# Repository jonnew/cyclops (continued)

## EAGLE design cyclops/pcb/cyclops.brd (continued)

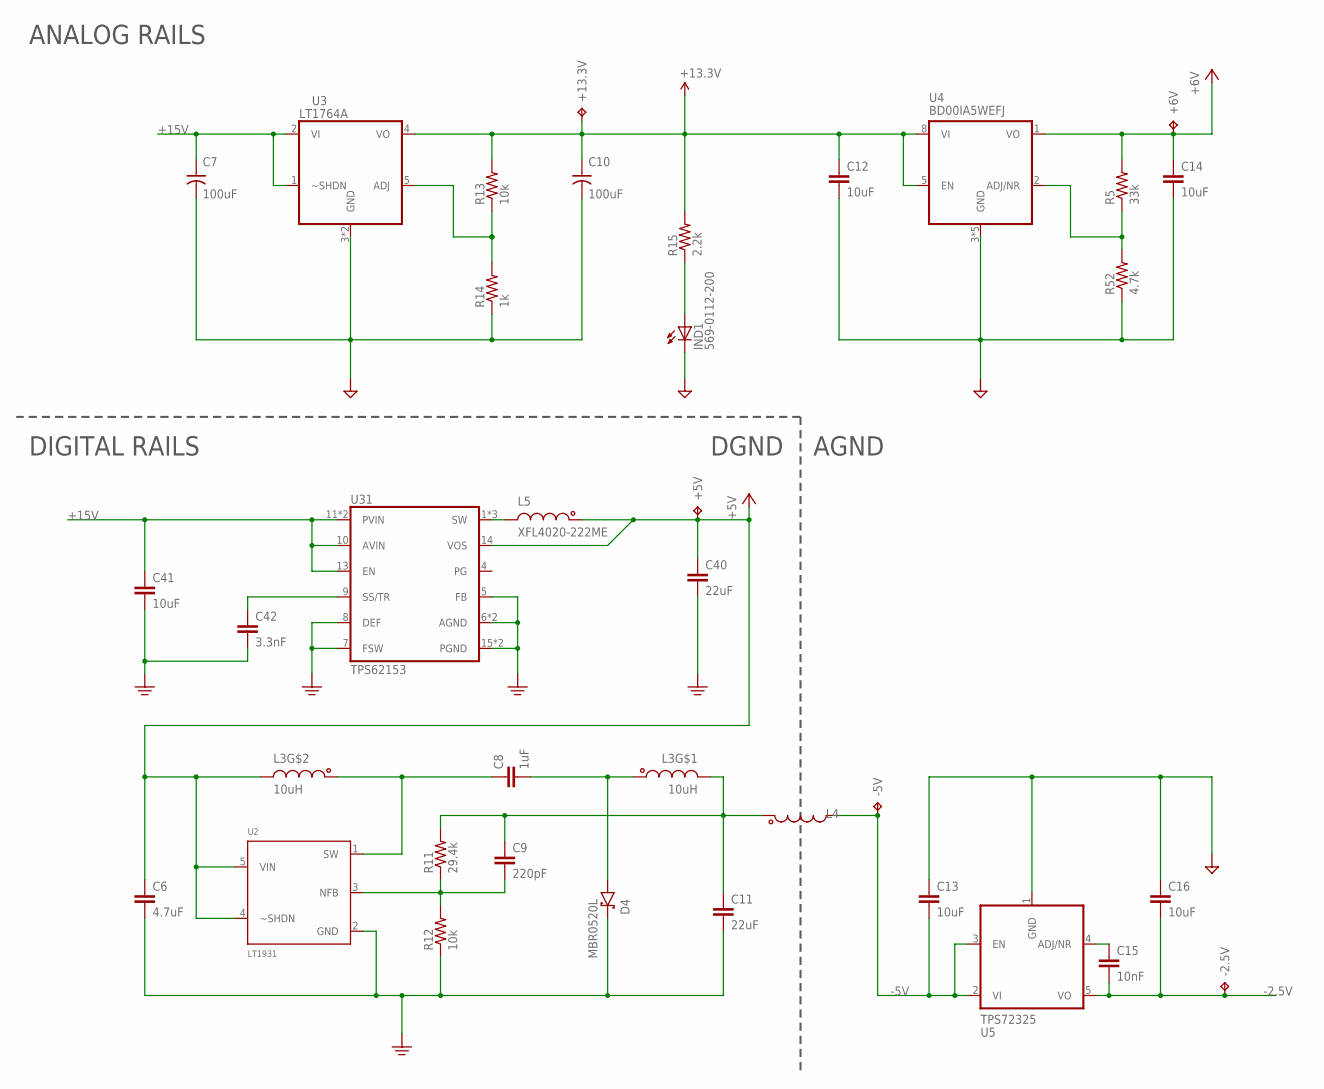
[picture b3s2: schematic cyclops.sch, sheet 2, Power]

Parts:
+5V, +6V, +13.3V: RCU-0C; RC0603
-2.5V, -5V: RCU-0C; RC0603
C6: 4.7uF; 1206
C7, C10: 100uF; 153CLV-0807
C8: 1uF; 1206
C9: 220pF; 0603
C11, C40: 22uF; 1210
C12, C13, C14, C16, C41: 10uF; 1206
C15: 10nF; 0603
C42: 3.3nF; 0603
D4: MBR0520L; SOD123
IND: 569-0112-200; 569-011X-X00_LED_ARRAY
L3: 10uH; CLS62
L4: MPZ1608; 0603
L5: XFL4020-222ME; 4020
R5: 33k; 0603
R11: 29.4k; 0603
R12, R13: 10k; 0603
R14: 1k; 0603
R15: 2.2k; 0603
R52: 4.7k; 0603
U2: LT1931; SOT95P310X175-5N
U3: LT1764A; 5-DDPAK
U4: BD00IA5WEFJ; SOIC127P600X175-9N
U5: TPS72325; SOT-23-5
U31: TPS62153; VQFN16

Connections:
+5V: +5V.1, C6.1, C40.1, L3.3 (2), L5.1, U2.4 (~SHDN), U2.5 (VIN), U31.14 (VOS); also elsewhere on the board
+6V: +6V.1, C14.1, R5.2, U4.1 (VO); also elsewhere on the board
+13.3V: +13.3V.1, C10.+, C12.1, R13.2, R15.2, U3.4 (VO), U4.5 (EN), U4.8 (VI); also elsewhere on the board
+15V: C7.+, C41.1, U3.1 (~SHDN), U3.2 (VI), U31.10 (AVIN), U31.11 (PVIN), U31.12 (PVIN), U31.13 (EN); also elsewhere on the board
-2.5V: -2.5V.1, C15.2, C16.2, U5.5 (VO); also elsewhere on the board
-5V: -5V.1, C13.2, L4.2, U5.2 (VI), U5.3 (EN); also elsewhere on the board
GND: C6.2, C7.-, C10.-, C11.2, C12.2, C13.1, C14.2, C16.1, C40.2, C41.2, C42.2, D4.C, IND.C1 (C), R12.1, R14.1, R52.1, U2.2 (GND), U3.3 (GND), U3.TAB (GND), U4.3 (GND), U4.4 (GND), U4.6 (GND), U4.7 (GND), U4.9 (GND), U5.1 (GND), U31.5 (FB), U31.6 (AGND), U31.7 (FSW), U31.8 (DEF), U31.15 (PGND), U31.16 (PGND), U31.PAD (AGND); also elsewhere on the board
unnamed: IND.A1 (A), R15.1
unnamed: R13.1, R14.2, U3.5 (ADJ)
unnamed: C8.1, L3.2 (1), U2.1 (SW)
unnamed: C8.2, D4.A, L3.1
unnamed: C9.1, C11.1, L3.4 (2), L4.1, R11.2
unnamed: C9.2, R11.1, R12.2, U2.3 (NFB)
unnamed: R5.1, R52.2, U4.2 (ADJ/NR)
unnamed: C15.1, U5.4 (ADJ/NR)
unnamed: C42.1, U31.9 (SS/TR)
SW: L5.2, U31.1 (SW), U31.2 (SW), U31.3 (SW)

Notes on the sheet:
ANALOG RAILS
DIGITAL RAILS
AGND
DGND

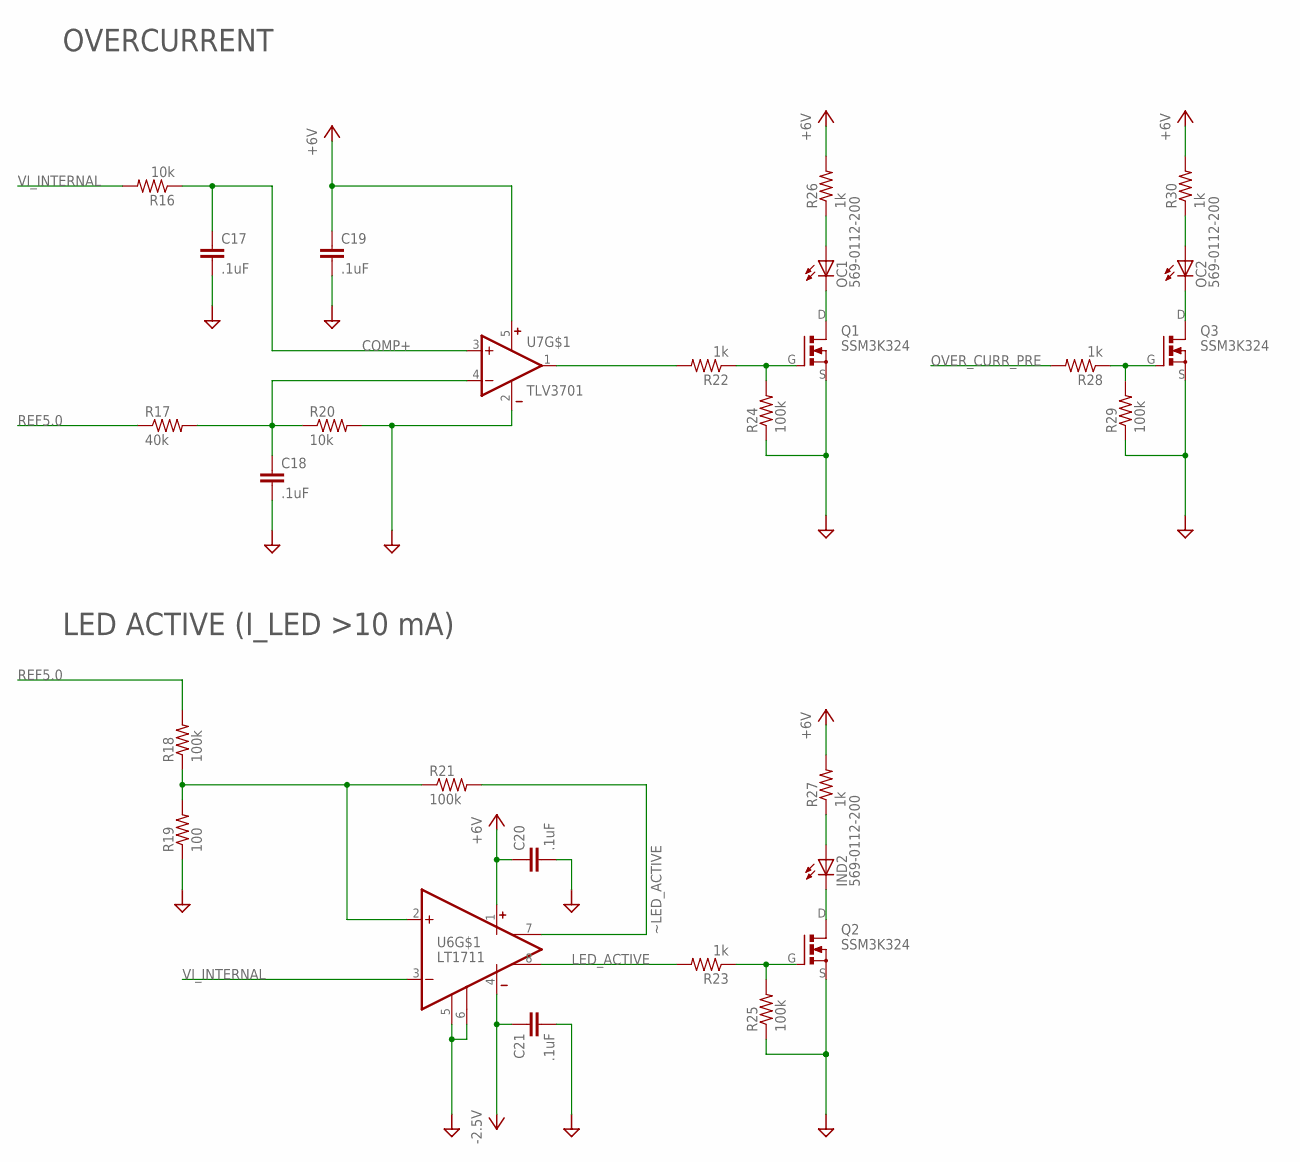
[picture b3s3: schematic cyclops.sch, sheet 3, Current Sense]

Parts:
C17, C18, C19, C20, C21: .1uF; 0603
IND: 569-0112-200; 569-011X-X00_LED_ARRAY
OC: 569-0112-200; 569-011X-X00_LED_ARRAY
Q1, Q2, Q3: SSM3K324; SOT23-GSD
R16, R20: 10k; 0603
R17: 40k; 0603
R18, R21, R24, R25, R29: 100k; 0603
R19: 100; 0603
R22, R23, R26, R27, R28, R30: 1k; 0603
U6: LT1711; SOP65P490X110-8N
U7: TLV3701; SOT-23-5

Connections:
+6V: C19.1, C20.1, R26.2, R27.2, R30.2, U6.1 (V+), U7.5 (V+); also elsewhere on the board
-2.5V: C21.1, U6.4 (V-); also elsewhere on the board
COMP+: C17.1, R16.1, U7.3 (+IN)
GND: C17.2, C18.2, C19.2, C20.2, C21.2, Q1.S, Q2.S, Q3.S, R19.1, R20.2, R24.1, R25.1, R29.1, U6.5 (LATCH), U6.6 (GND), U7.2 (V-); also elsewhere on the board
LED_ACTIVE: R23.2, U6.8 (~Q); also elsewhere on the board
unnamed: OC.A1 (A), R26.1
unnamed: C18.1, R17.2, R20.1, U7.4 (-IN)
unnamed: OC.C1 (C), Q1.D
unnamed: OC.A2 (A), R30.1
unnamed: R22.2, U7.1 (OUT)
unnamed: Q1.G, R22.1, R24.2
unnamed: Q3.G, R28.1, R29.2
unnamed: R18.1, R19.2, R21.1, U6.2 (+IN)
unnamed: IND.A2 (A), R27.1
unnamed: IND.C2 (C), Q2.D
unnamed: Q2.G, R23.1, R25.2
OC: OC.C2 (C), Q3.D
OVER_CURR_PRE: R28.2; also elsewhere on the board
REF5.0: R17.1, R18.2; also elsewhere on the board
VI_INTERNAL: R16.2, U6.3 (-IN); also elsewhere on the board
~LED_ACTIVE: R21.2, U6.7 (Q)

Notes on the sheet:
LED ACTIVE (I_LED >10 mA)
OVERCURRENT

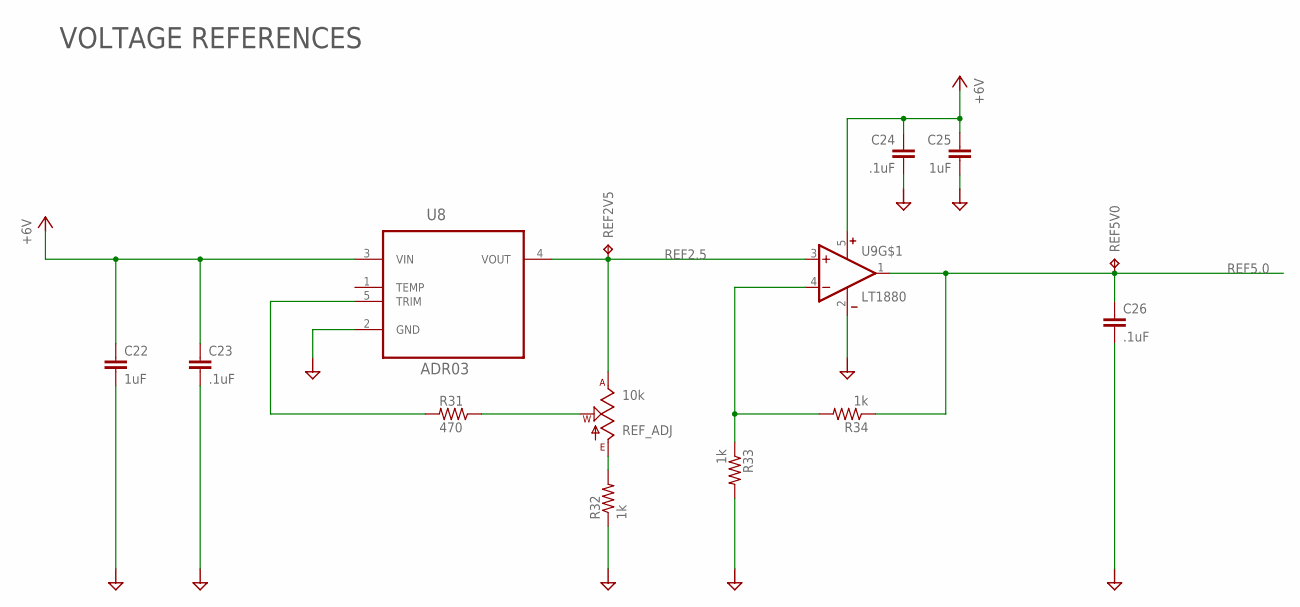
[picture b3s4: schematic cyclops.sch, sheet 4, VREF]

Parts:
C22, C25: 1uF; 0805
C23, C24, C26: .1uF; 0603
R31: 470; 0603
R32, R33, R34: 1k; 0603
REF2V5, REF5V0: RCU-0C; RC0603
REF_ADJ: 10k; SM-42/43W
U8: ADR03; SOT65P210X110-5N
U9: LT1880; SOT95P310X175-5N

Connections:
+6V: C22.1, C23.1, C24.1, C25.1, U8.3 (VIN), U9.5 (V+); also elsewhere on the board
GND: C22.2, C23.2, C24.2, C25.2, C26.2, R32.1, R33.2, U8.2 (GND), U9.2 (V-); also elsewhere on the board
unnamed: R32.2, REF_ADJ.3 (E)
unnamed: R33.1, R34.2, U9.4 (-IN)
unnamed: R31.2, U8.5 (TRIM)
unnamed: R31.1, REF_ADJ.2 (W)
REF2.5: REF2V5.1, REF_ADJ.1 (A), U8.4 (VOUT), U9.3 (+IN); also elsewhere on the board
REF5.0: C26.1, R34.1, REF5V0.1, U9.1 (OUT); also elsewhere on the board

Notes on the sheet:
VOLTAGE REFERENCES

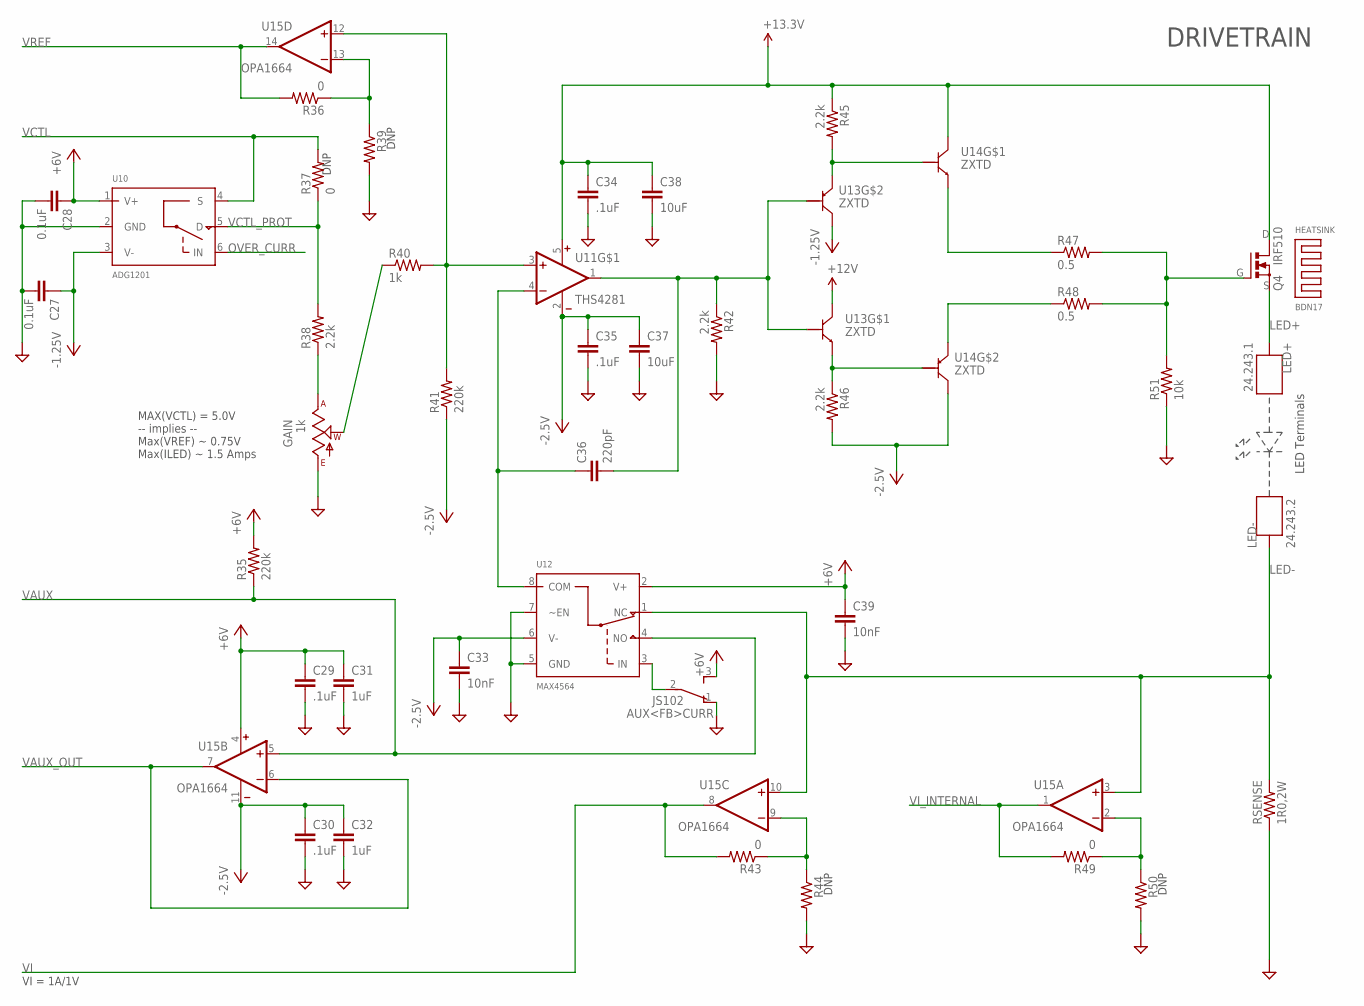
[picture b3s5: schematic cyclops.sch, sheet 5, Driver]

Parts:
AUX<FB>CURR: JS102; JS102011SAQN
C27, C28: 0.1uF; 0603
C29, C30, C34, C35: .1uF; 0603
C31, C32: 1uF; 0805
C33, C39: 10nF; 0603
C36: 220pF; 0603
C37, C38: 10uF; 1206
GAIN: 1k; 3310C-001
HEATSINK: BDN17
LED+: 24.243.1; A-2107
LED-: 24.243.2; A-2107
Q4: IRF510; TO-262_01
R35, R41: 220k; 0603
R36, R37, R43, R49: 0; 0603
R38, R42, R45, R46: 2.2k; 0603
R39, R44, R50: R_0603; 0603
R40: 1k; 0603
R47, R48: 0.5; 0603
R51: 10k; 0603
RSENSE: 1R0,2W; 2512
U10: ADG1201; SOT23-6
U11: THS4281; SOT95P310X175-5N
U12: MAX4564; SOT65P300X175-N
U13, U14: ZXTD; SOT23-6
U15: OPA1664; SO14

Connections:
+6V: AUX<FB>CURR.3, C28.1, C29.1, C31.1, C39.1, R35.2, U10.1 (V+), U12.2 (V+), U15.4 (V+); also elsewhere on the board
+13.3V: C34.1, C38.1, Q4.D, R45.1, U11.5 (V+), U13.1 (C), U14.1 (C); also elsewhere on the board
-2.5V: C27.1, C30.1, C32.1, C33.1, C35.1, C37.1, R41.1, R46.2, U10.3 (V-), U11.2 (V-), U12.6 (V-), U13.3 (C), U14.3 (C), U15.11 (V-); also elsewhere on the board
COM: C36.1, U11.4 (-IN), U12.8 (COM)
GND: AUX<FB>CURR.1, C27.2, C28.2, C29.2, C30.2, C31.2, C32.2, C33.2, C34.2, C35.2, C37.2, C38.2, C39.2, GAIN.1 (E), R39.2, R42.2, R44.2, R50.2, R51.1, RSENSE.1, U10.2 (GND), U12.5 (GND), U12.7 (~EN); also elsewhere on the board
IN: AUX<FB>CURR.2, U12.3 (IN)
LED+: LED+.1, LED+.2, Q4.S; also elsewhere on the board
LED-: LED-.1, LED-.2, RSENSE.2, U12.1 (NC), U15.3 (+IN), U15.10 (+IN); also elsewhere on the board
unnamed: R45.2, U13.4 (E), U14.2 (B)
unnamed: R36.1, R39.1, U15.13 (-IN)
unnamed: R46.1, U13.6 (E), U14.5 (B)
unnamed: R49.1, R50.1, U15.2 (-IN)
unnamed: C36.2, R42.1, U11.1 (OUT), U13.2 (B), U13.5 (B)
unnamed: R43.1, R44.1, U15.9 (-IN)
unnamed: R48.1, U14.4 (E)
unnamed: R47.1, U14.6 (E)
unnamed: Q4.G, R47.2, R48.2, R51.2
unnamed: GAIN.2 (W), R40.1
OVER_CURR: U10.6 (IN); also elsewhere on the board
VAUX: R35.1, U12.4 (NO), U15.5 (+IN); also elsewhere on the board
VAUX_OUT: U15.6 (-IN), U15.7 (OUT); also elsewhere on the board
VCTL: R37.2, U10.4 (S); also elsewhere on the board
VCTL_PROT: R37.1, R38.2, U10.5 (D)
VCTL_PROTECT: GAIN.3 (A), R38.1
VI: R43.2, U15.8 (OUT); also elsewhere on the board
VI_INTERNAL: R49.2, U15.1 (OUT); also elsewhere on the board
VREF: R36.2, U15.14 (OUT); also elsewhere on the board
_VREF: R40.2, R41.2, U11.3 (+IN), U15.12 (+IN)

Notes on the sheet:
LED Terminals
MAX(VCTL) = 5.0V -- implies -- Max(VREF) ~ 0.75V Max(ILED) ~ 1.5 Amps
VI = 1A/1V
DRIVETRAIN
DNP

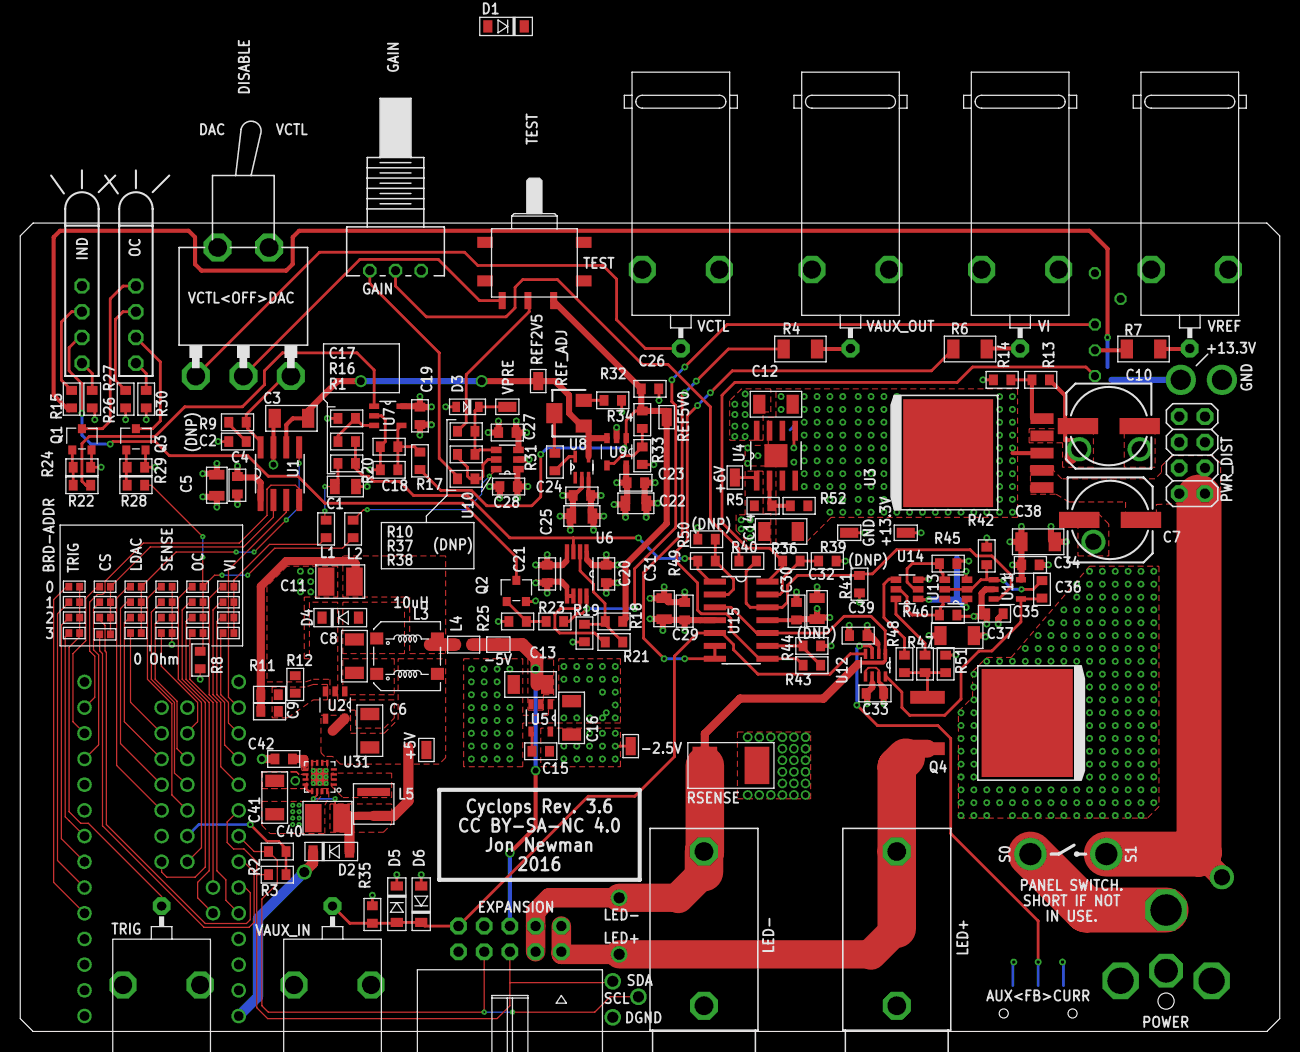
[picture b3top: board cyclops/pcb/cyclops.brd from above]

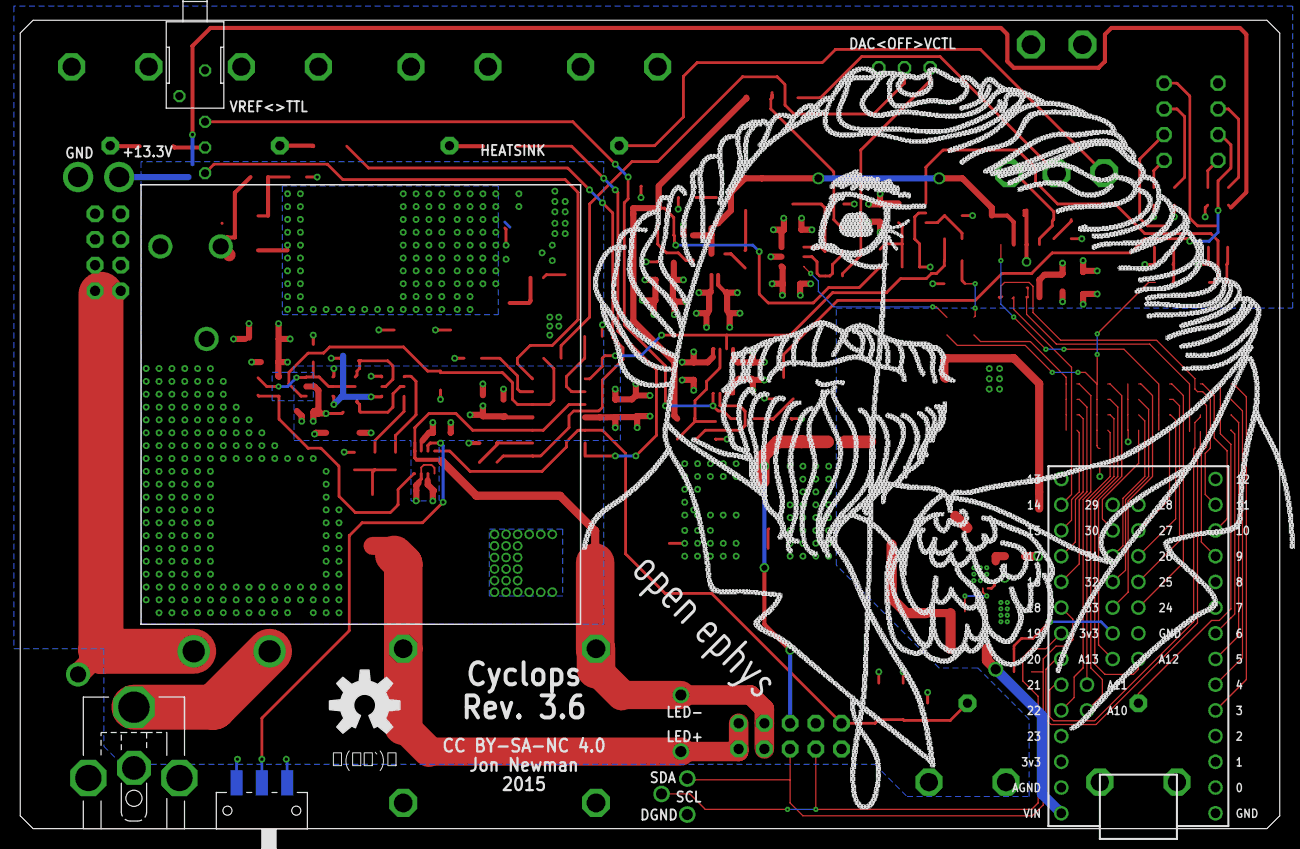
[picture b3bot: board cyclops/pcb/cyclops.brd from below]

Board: 4 copper layers, 124.5 x 79.9 mm, 183 parts (8 on the bottom side), 107 nets.

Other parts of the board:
U$30: OPEN_EPHYS_LOGO
U$56: CYCLOPS_LOGO
U$60: OSHW-LOGO-L

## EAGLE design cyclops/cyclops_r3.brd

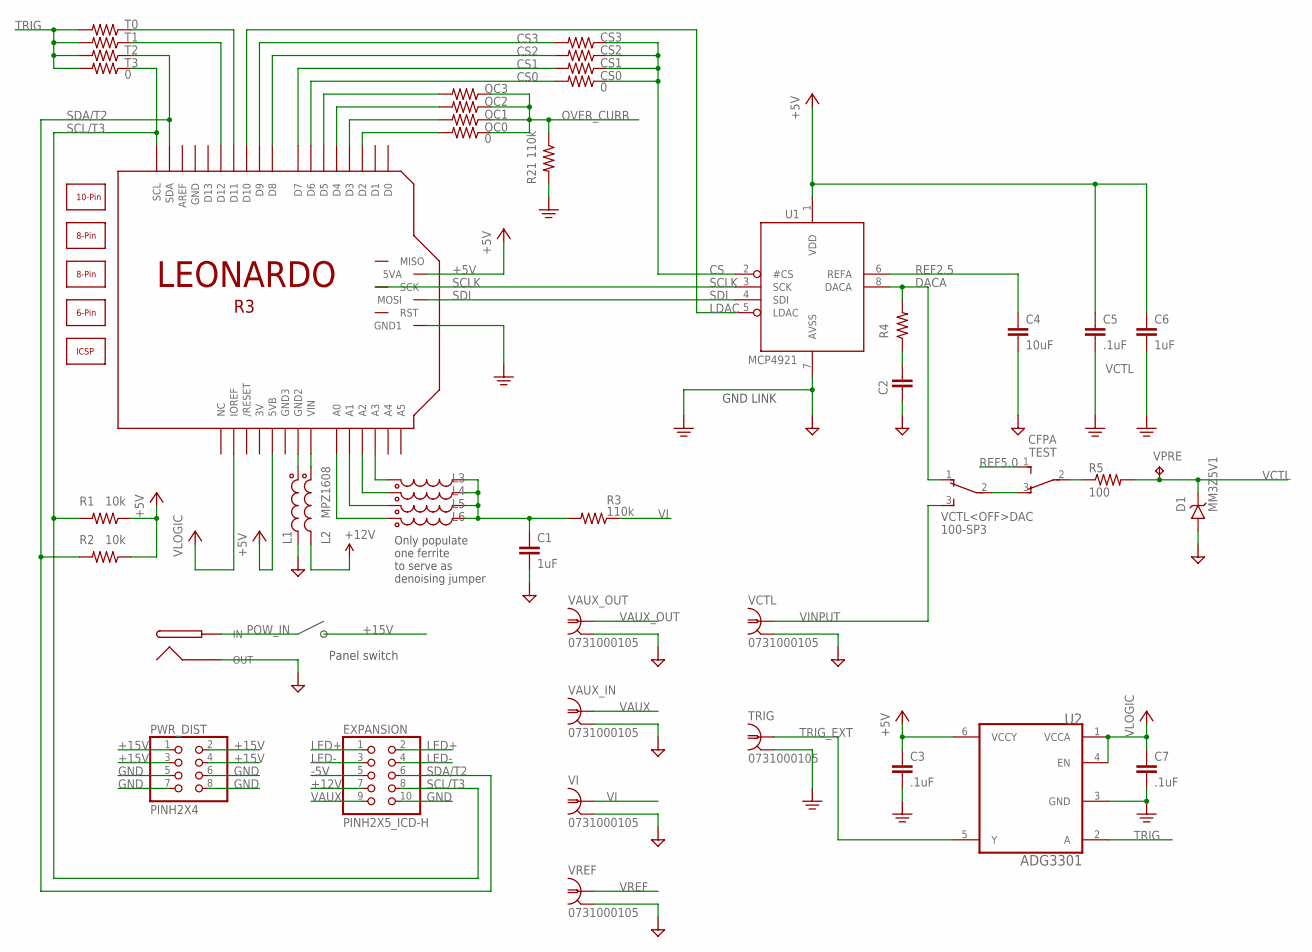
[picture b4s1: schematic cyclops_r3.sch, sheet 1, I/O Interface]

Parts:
C1, C6: 1uF; 0805
C2: C_0603; 0603
C3, C5, C7: .1uF; 0603
C4: 10uF; 1206
CS0, CS1, CS2, CS3: 0; 0603
D1: MM3Z5V1; SOD-323
EXPANSION: PINH2X5_ICD-H; 2X05-IDC
L1, L2, L3, L4, L5, L6: MPZ1608; 0603
LEONARDO: LEONARDO_R3_ICSP; ARDUINOR3_PINS_NOHOLES
OC0, OC1, OC2, OC3: 0; 0603
POWER: PJ-063BH
PWR_DIST: PINH2X4; 2X04-BIG
R1, R2: 10k; 0603
R3, R21: 110k; 0603
R4: R_0603; 0603
R5: 100; 0603
T0, T1, T2, T3: 0; 0603
TEST: CFPA
TRIG: 0731000105
U1: MCP4921; SO08
U2: ADG3301; SOT65P210X110-6N
VAUX_IN: 0731000105
VAUX_OUT: 0731000105
VCTL: 0731000105
VCTL<OFF>DAC: 100-SP3; 2M1-SP1-T2-B4-M6RE
VI: 0731000105
VPRE: TPTP16R; TP16R
VREF: 0731000105

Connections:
+5V: C3.1, C5.1, C6.1, LEONARDO.5VA, LEONARDO.5VB, R1.1, R2.1, U1.1 (VDD), U2.6 (VCCY)
+12V: EXPANSION.7, L2.2; also elsewhere on the board
+15V: PWR_DIST.1, PWR_DIST.2, PWR_DIST.3, PWR_DIST.4; also elsewhere on the board
-5V: EXPANSION.5; also elsewhere on the board
CS: CS0.1, CS1.1, CS2.1, CS3.1, U1.2 (#CS)
CS0: CS0.2, LEONARDO.D6
CS1: CS1.2, LEONARDO.D7
CS2: CS2.2, LEONARDO.D8
CS3: CS3.2, LEONARDO.D9
DACA: R4.2, U1.8 (DACA), VCTL<OFF>DAC.1
GND: C1.2, C2.2, C3.2, C4.2, C5.2, C6.2, C7.2, D1.A, EXPANSION.10, L1.2, LEONARDO.GND1, POWER.2 (OUT), PWR_DIST.5, PWR_DIST.6, PWR_DIST.7, PWR_DIST.8, R21.2, TRIG.2, TRIG.3 (2), U1.7 (AVSS), U2.3 (GND), VAUX_IN.2, VAUX_IN.3 (2), VAUX_OUT.2, VAUX_OUT.3 (2), VCTL.2, VCTL.3 (2), VI.2, VI.3 (2), VREF.2, VREF.3 (2); also elsewhere on the board
KEEPOUT_GND: L1.1, LEONARDO.GND2
LDAC: LEONARDO.D10, U1.5 (LDAC)
LED+: EXPANSION.1, EXPANSION.2; also elsewhere on the board
LED-: EXPANSION.3, EXPANSION.4; also elsewhere on the board
unnamed: C2.1, R4.1
unnamed: L6.1, LEONARDO.A0
unnamed: C1.1, L3.2, L4.2, L5.2, L6.2, R3.2
unnamed: R5.1, TEST.2
unnamed: L5.1, LEONARDO.A1
unnamed: L4.1, LEONARDO.A2
unnamed: L3.1, LEONARDO.A3
unnamed: TEST.3 (1), VCTL<OFF>DAC.2
unnamed: LEONARDO.D2, OC0.2
OC0: LEONARDO.D3, OC1.2
OC1: LEONARDO.D4, OC2.2
OC2: LEONARDO.D5, OC3.2
OVER_CURR: OC0.1, OC1.1, OC2.1, OC3.1, R21.1; also elsewhere on the board
POW_IN: POWER.1 (IN)
REF2.5: C4.1, U1.6 (REFA); also elsewhere on the board
REF5.0: TEST.1 (3); also elsewhere on the board
SCL/T3: EXPANSION.8, LEONARDO.SCL, R1.2, T3.1
SCLK: LEONARDO.SCK, U1.3 (SCK)
SDA/T2: EXPANSION.6, LEONARDO.SDA, R2.2, T2.1
SDI: LEONARDO.MOSI, U1.4 (SDI)
T0: LEONARDO.D11, T0.1
T1: LEONARDO.D12, T1.1
TRIG: T0.2, T1.2, T2.2, T3.2, U2.2 (A)
TRIG_EXT: TRIG.1, U2.5 (Y)
VAUX: EXPANSION.9, VAUX_IN.1; also elsewhere on the board
VAUX_OUT: VAUX_OUT.1; also elsewhere on the board
VCTL: D1.C, R5.2, VPRE.TP; also elsewhere on the board
VI: R3.1, VI.1; also elsewhere on the board
VINPUT: VCTL.1, VCTL<OFF>DAC.3
VIN_ARDUINO: L2.1, LEONARDO.VIN; also elsewhere on the board
VLOGIC: C7.1, LEONARDO.IOREF, U2.1 (VCCA), U2.4 (EN)
VREF: VREF.1; also elsewhere on the board

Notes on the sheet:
GND LINK
Only populate one ferrite to serve as denoising jumper
Panel switch

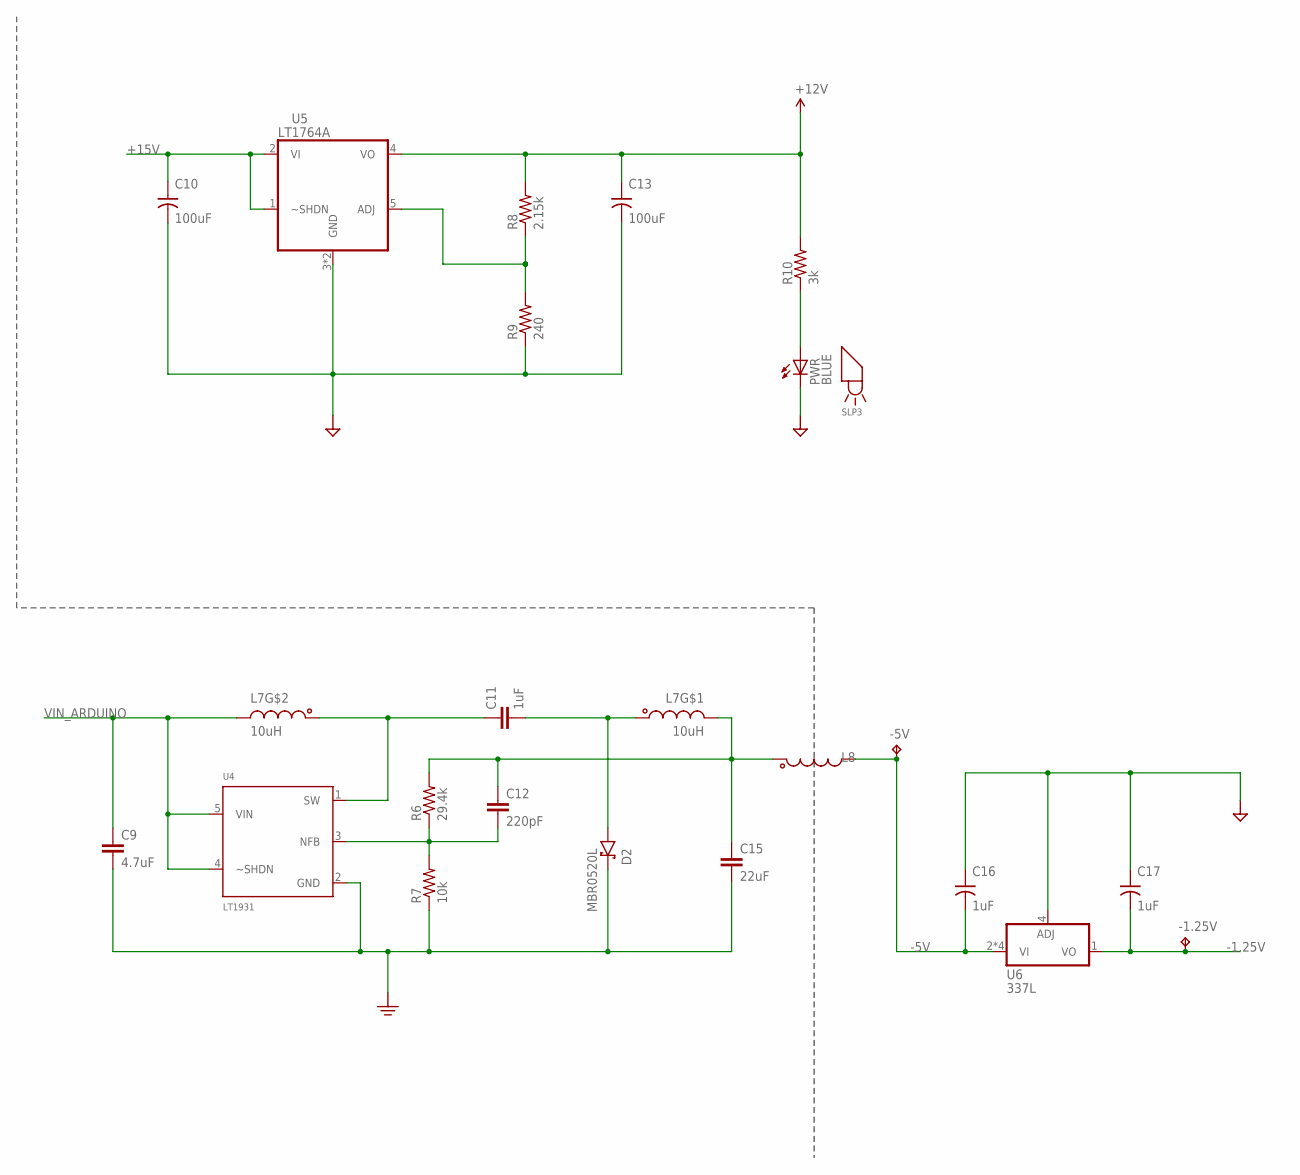
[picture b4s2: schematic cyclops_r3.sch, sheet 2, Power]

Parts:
-1.25V, -5V: TPTP16R; TP16R
C9: 4.7uF; 1206
C10, C13: 100uF; 153CLV-0807
C11: 1uF; 1206
C12: 220pF; 0603
C15: 22uF; 1210
C16, C17: 1uF; 1206-POL
D2: MBR0520L; SOD123
L7: 10uH; CLS62
L8: MPZ1608; 0603
PWR: BLUE; LED-0603
R6: 29.4k; 0603
R7: 10k; 0603
R8: 2.15k; 0603
R9: 240; 0603
R10: 3k; 0603
U4: LT1931; SOT95P310X175-5N
U5: LT1764A; 5-DDPAK
U6: 337L; SOIC127P600X175-8N
X1: SLP3; SL3P-150-100-F

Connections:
+12V: C13.+, R8.2, R10.2, U5.4 (VO); also elsewhere on the board
+15V: C10.+, U5.1 (~SHDN), U5.2 (VI); also elsewhere on the board
-1.25V: -1.25V.TP, C17.-, U6.1 (VO); also elsewhere on the board
-5V: -5V.TP, C16.-, L8.2, U6.2 (VI), U6.3 (VI), U6.6 (VI), U6.7 (VI); also elsewhere on the board
GND: C9.2, C10.-, C13.-, C15.2, C16.+, C17.+, D2.C, PWR.C, R7.1, R9.1, U4.2 (GND), U5.3 (GND), U5.TAB (GND), U6.4 (ADJ); also elsewhere on the board
unnamed: PWR.A, R10.1
unnamed: R8.1, R9.2, U5.5 (ADJ)
unnamed: C11.1, L7.2 (1), U4.1 (SW)
unnamed: C11.2, D2.A, L7.1
unnamed: C12.1, C15.1, L7.4 (2), L8.1, R6.2
unnamed: C12.2, R6.1, R7.2, U4.3 (NFB)
VIN_ARDUINO: C9.1, L7.3 (2), U4.4 (~SHDN), U4.5 (VIN); also elsewhere on the board

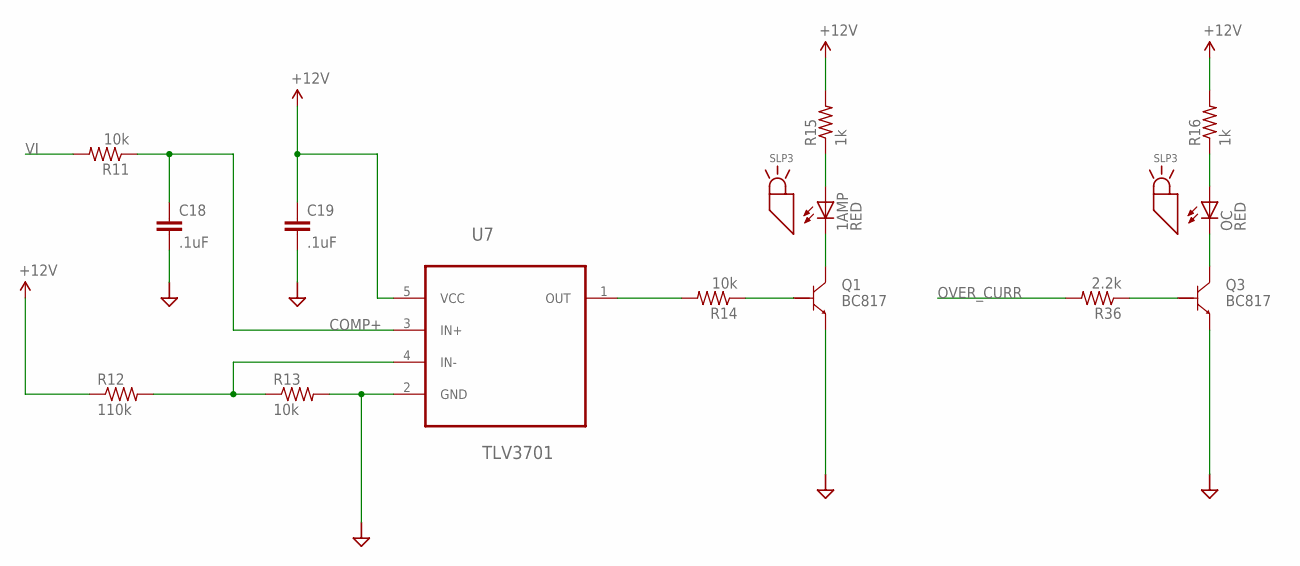
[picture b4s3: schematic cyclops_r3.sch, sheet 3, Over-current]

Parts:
1AMP: RED; LED-0603
C18, C19: .1uF; 0603
OC: RED; LED-0603
Q1, Q3: BC817; SOT23-BEC
R11, R13, R14: 10k; 0603
R12: 110k; 0603
R15, R16: 1k; 0603
R36: 2.2k; 0603
U7: TLV3701; SOT95P280X145-5N
X2, X3: SLP3; SL3P-150-100-F

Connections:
+12V: C19.1, R12.1, R15.2, R16.2, U7.5 (VCC); also elsewhere on the board
COMP+: C18.1, R11.1, U7.3 (IN+)
GND: C18.2, C19.2, Q1.E, Q3.E, R13.2, U7.2 (GND); also elsewhere on the board
unnamed: 1AMP.A, R15.1
unnamed: R12.2, R13.1, U7.4 (IN-)
unnamed: 1AMP.C, Q1.C
unnamed: OC.A, R16.1
unnamed: R14.2, U7.1 (OUT)
unnamed: Q1.B, R14.1
unnamed: OC.C, Q3.C
unnamed: Q3.B, R36.1
OVER_CURR: R36.2; also elsewhere on the board
VI: R11.2; also elsewhere on the board

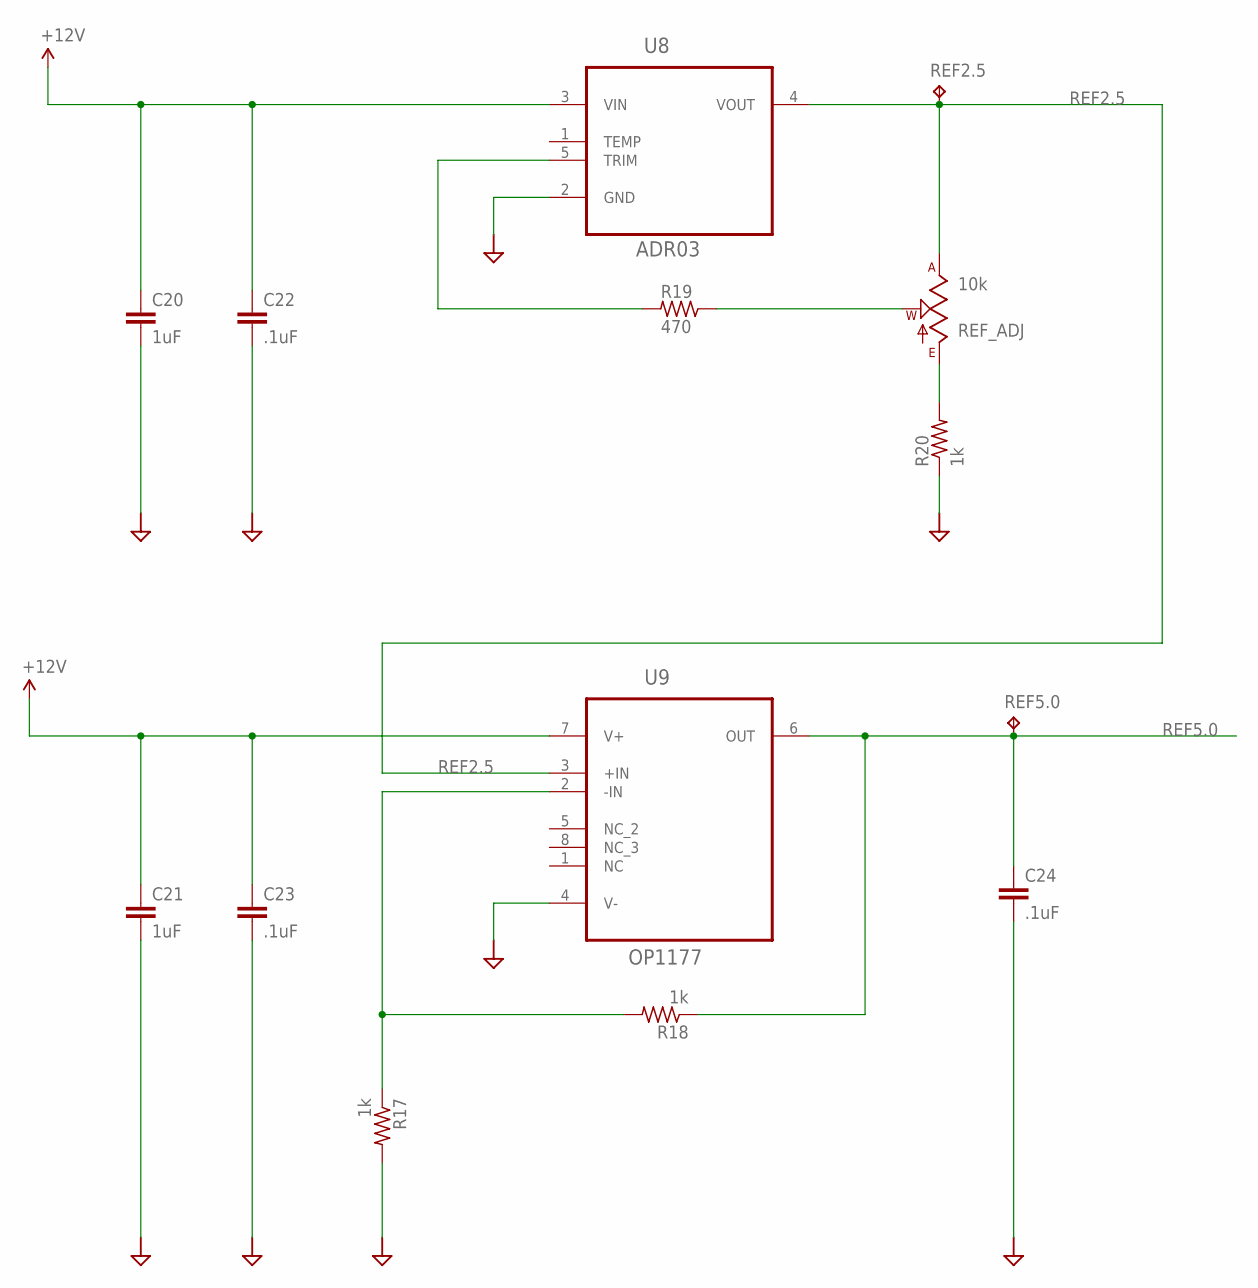
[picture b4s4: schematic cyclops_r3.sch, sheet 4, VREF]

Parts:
C20, C21: 1uF; 0805
C22, C23, C24: .1uF; 0603
R17, R18, R20: 1k; 0603
R19: 470; 0603
REF2.5, REF5.0: TPTP16R; TP16R
REF_ADJ: 10k; SM-42/43W
U8: ADR03; SOT65P210X110-5N
U9: OP1177; SOP65P490X110-8N

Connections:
+12V: C20.1, C21.1, C22.1, C23.1, U8.3 (VIN), U9.7 (V+); also elsewhere on the board
GND: C20.2, C21.2, C22.2, C23.2, C24.2, R17.2, R20.1, U8.2 (GND), U9.4 (V-); also elsewhere on the board
unnamed: R20.2, REF_ADJ.3 (E)
unnamed: R17.1, R18.2, U9.2 (-IN)
unnamed: R19.2, U8.5 (TRIM)
unnamed: R19.1, REF_ADJ.2 (W)
REF2.5: REF2.5.TP, REF_ADJ.1 (A), U8.4 (VOUT), U9.3 (+IN); also elsewhere on the board
REF5.0: C24.1, R18.1, REF5.0.TP, U9.6 (OUT); also elsewhere on the board

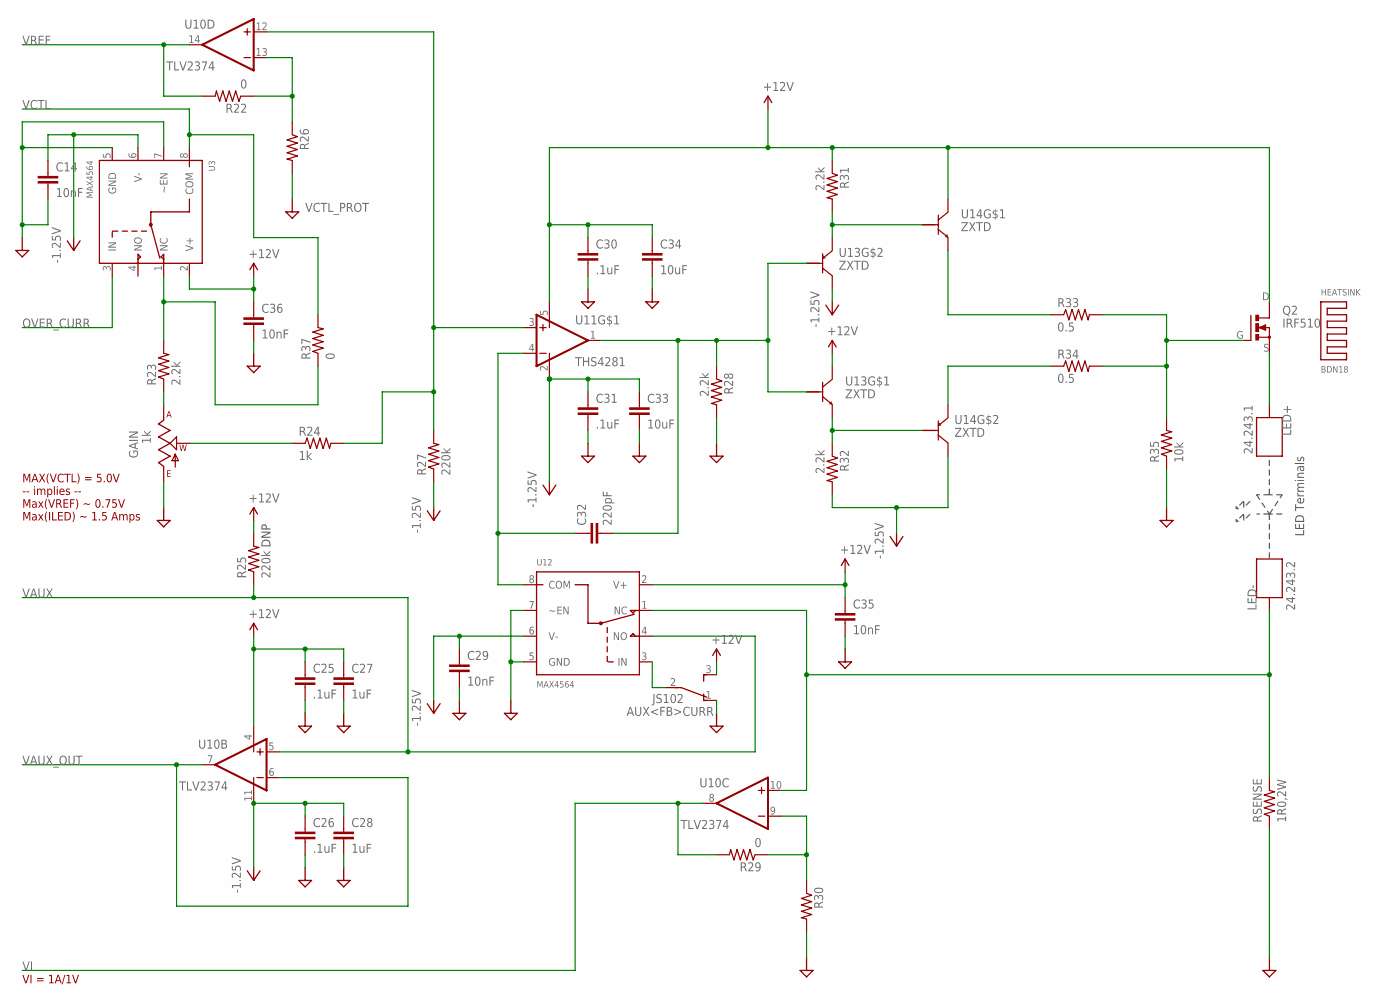
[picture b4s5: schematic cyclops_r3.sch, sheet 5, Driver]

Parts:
AUX<FB>CURR: JS102; JS102011SAQN
C14, C29, C35, C36: 10nF; 0603
C25, C26, C30, C31: .1uF; 0603
C27, C28: 1uF; 0805
C32: 220pF; 0603
C33, C34: 10uF; 1206
GAIN: 1k; 3310C-001
HEATSINK: BDN18
LED+: 24.243.1; A-2107
LED-: 24.243.2; A-2107
Q2: IRF510; TO-262_01
R22, R29, R37: 0; 0603
R23, R28, R31, R32: 2.2k; 0603
R24: 1k; 0603
R25, R27: 220k; 0603
R26, R30: R_0603; 0603
R33, R34: 0.5; 0603
R35: 10k; 0603
RSENSE: 1R0,2W; 2512
U3, U12: MAX4564; SOT65P300X175-N
U10: TLV2374; SO14
U11: THS4281; SOT95P310X175-5N
U13, U14: ZXTD; SOT23-6

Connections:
+12V: AUX<FB>CURR.3, C25.1, C27.1, C30.1, C34.1, C35.1, C36.1, Q2.D, R25.2, R31.1, U3.2 (V+), U10.4 (V+), U11.5 (V+), U12.2 (V+), U13.1 (C), U14.1 (C); also elsewhere on the board
-1.25V: C14.1, C26.1, C28.1, C29.1, C31.1, C33.1, R27.1, R32.2, U3.6 (V-), U10.11 (V-), U11.2 (V-), U12.6 (V-), U13.3 (C), U14.3 (C); also elsewhere on the board
COM: C32.1, U11.4 (-IN), U12.8 (COM)
GND: AUX<FB>CURR.1, C14.2, C25.2, C26.2, C27.2, C28.2, C29.2, C30.2, C31.2, C33.2, C34.2, C35.2, C36.2, GAIN.1 (E), R26.2, R28.2, R30.2, R35.1, RSENSE.1, U3.5 (GND), U3.7 (~EN), U12.5 (GND), U12.7 (~EN); also elsewhere on the board
IN: AUX<FB>CURR.2, U12.3 (IN)
LED+: LED+.1, LED+.2, Q2.S; also elsewhere on the board
LED-: LED-.1, LED-.2, RSENSE.2, U10.10 (+IN), U12.1 (NC); also elsewhere on the board
unnamed: R31.2, U13.4 (E), U14.2 (B)
unnamed: R22.1, R26.1, U10.13 (-IN)
unnamed: R32.1, U13.6 (E), U14.5 (B)
unnamed: C32.2, R28.1, U11.1 (OUT), U13.2 (B), U13.5 (B)
unnamed: R29.1, R30.1, U10.9 (-IN)
unnamed: R34.1, U14.4 (E)
unnamed: R33.1, U14.6 (E)
unnamed: Q2.G, R33.2, R34.2, R35.2
unnamed: GAIN.2 (W), R24.1
OVER_CURR: U3.3 (IN); also elsewhere on the board
VAUX: R25.1, U10.5 (+IN), U12.4 (NO); also elsewhere on the board
VAUX_OUT: U10.6 (-IN), U10.7 (OUT); also elsewhere on the board
VCTL: R37.2, U3.8 (COM); also elsewhere on the board
VCTL_PROT: R23.2, R37.1, U3.1 (NC)
VCTL_PROTECT: GAIN.3 (A), R23.1
VI: R29.2, U10.8 (OUT); also elsewhere on the board
VREF: R22.2, U10.14 (OUT); also elsewhere on the board
_VREF: R24.2, R27.2, U10.12 (+IN), U11.3 (+IN)

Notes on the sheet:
LED Terminals
MAX(VCTL) = 5.0V -- implies -- Max(VREF) ~ 0.75V Max(ILED) ~ 1.5 Amps
VI = 1A/1V
DNP
